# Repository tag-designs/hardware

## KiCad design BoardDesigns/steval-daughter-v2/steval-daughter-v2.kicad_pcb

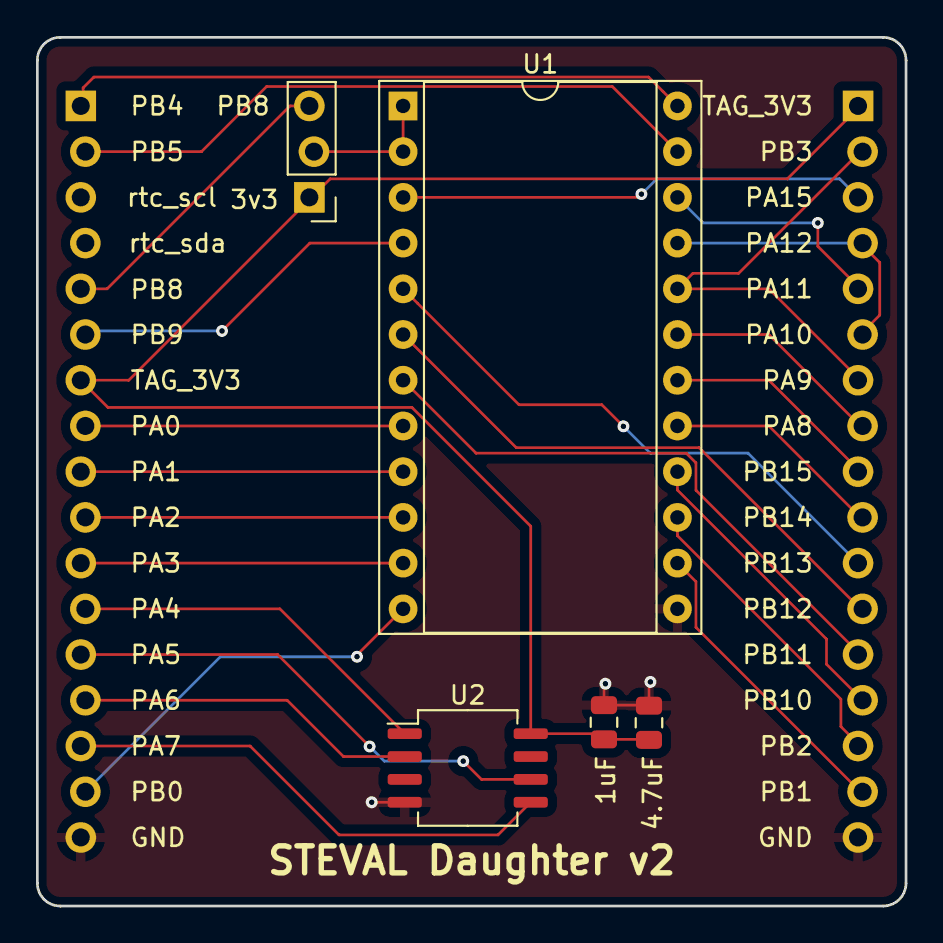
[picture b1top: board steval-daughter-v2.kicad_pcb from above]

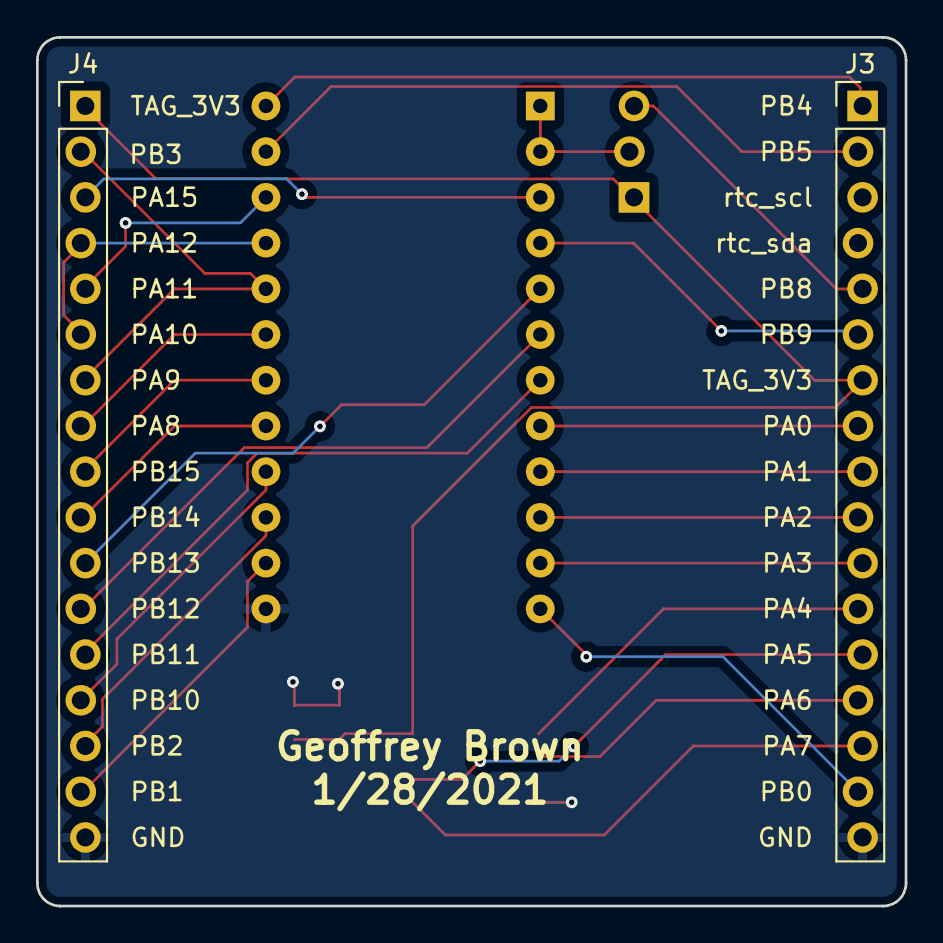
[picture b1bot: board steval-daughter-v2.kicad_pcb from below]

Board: 2 copper layers, 48.3 x 48.3 mm, 7 parts (2 on the bottom side), 29 nets.

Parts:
C1: 4.7uF; C_0805_2012Metric
C2: 1uF; C_0805_2012Metric
J3, J4: Conn_01x17; PinHeader_1x17_P2.54mm_Vertical_Staggered
J101: Conn_01x03; PinHeader_1x03_P2.54mm_Vertical
U1: ST-Steval; DIP-24_W15.24mm_Socket
U2: AT25FF321; SO-8_5.3x6.2mm_P1.27mm

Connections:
/PA0: J3.8, U1.8
/PA1: J3.9, U1.9
/PA2: J3.10, U1.10
/PA3: J3.11, U1.11
/PA4: J3.12, U2.1
/PA5: J3.13, U2.6
/PA6: J3.14, U2.2
/PA7: J3.15, U2.5
/PA8: J4.8, U1.19
/PA9: J4.2, J4.7, U1.20
/PA10: J4.4, J4.6, U1.21
/PA11: J4.5, U1.22
/PA15: J4.3, U1.3
/PB0: J3.16, U1.12
/PB1: J4.16, U1.14
/PB2: J4.15, U1.15
/PB4: J3.1, U1.24
/PB5: J3.2, U1.23
/PB8: J3.5, J101.3
/PB9: J3.6, U1.4
/PB10: J4.14, U1.16
/PB11: J4.13, U1.7
/PB12: J4.12, U1.6
/PB13: J4.11, U1.5
/PB14: J4.10, U1.17
/PB15: J4.9, U1.18
/TAG_3V3: C1.1, C2.1, J3.7, J4.1, J101.1, U2.8
GND: C1.2, C2.2, J3.17, J4.17, U1.13, U2.4
unnamed: J101.2, U1.1, U1.2

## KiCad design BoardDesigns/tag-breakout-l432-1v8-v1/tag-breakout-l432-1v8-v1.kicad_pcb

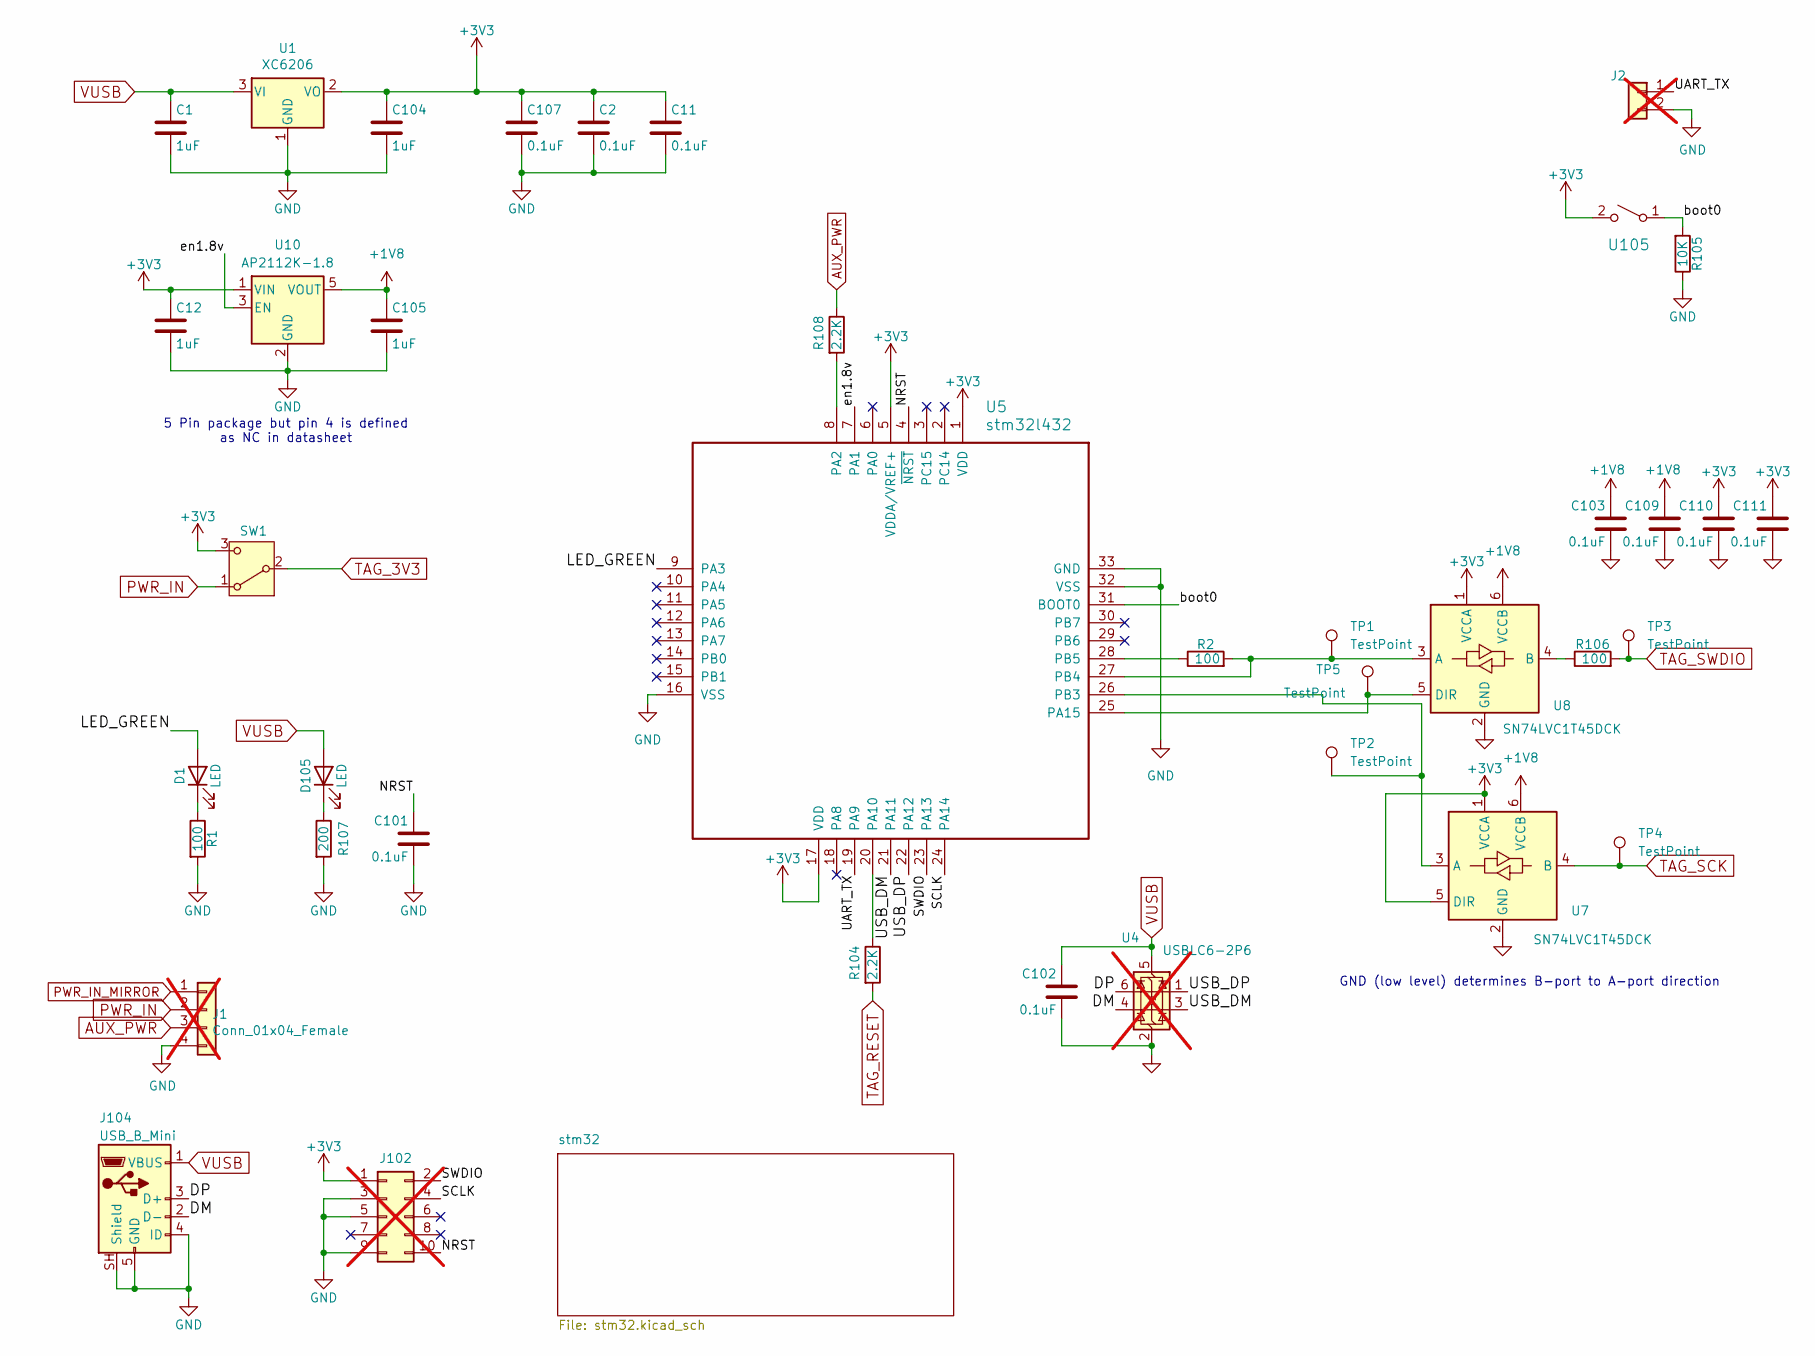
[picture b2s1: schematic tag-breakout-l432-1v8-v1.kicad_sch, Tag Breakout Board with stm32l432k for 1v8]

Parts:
C1, C12, C104, C105: 1uF; C_0402_1005Metric; MPN CL05A105KA5NQNC; LCSC C52923
C2, C11, C101, C102, C103, C107, C109, C110, C111: 0.1uF; C_0402_1005Metric; MPN CL05B104KO5NNNC; LCSC C1525
D1: LED; LED_0805_2012Metric; MPN KT-0805G; LCSC C2297
D105: LED; LED_0603_1608Metric; MPN KT-0603R; LCSC C2286
J1: Conn_01x04_Female; JST_XH_B04B-XH-AM_1x04_P2.50mm_Vertical; not fitted
J2: Conn_01x02_Male; PinHeader_1x02_P2.54mm_Vertical; not fitted
J102: Conn_02x05_Odd_Even; FTSH-105-01-F-D-K; not fitted
J104: USB_B_Mini; USB_Mini-B_Lumberg_2486_01_Horizontal; MPN MINI 5PTP; LCSC C2681563
R1, R2, R106: 100; R_0402_1005Metric; MPN 0402WGF1000TCE; LCSC C25076
R104, R108: 2.2K; R_0402_1005Metric; MPN 0402WGF2201TCE; LCSC C25879
R105: 10K; R_0402_1005Metric; MPN 0402WGF1002TCE; LCSC C25744
R107: 200; R_0402_1005Metric; MPN 0402WGF2000TCE; LCSC C25087
SW1: SW_SPDT; CJS-1200B_NDC; MPN CJS-1200B2; LCSC C35817163
TP1, TP2, TP3, TP4, TP5: TestPoint; TestPoint_Pad_D2.5mm
U1: XC6206; SOT-23-3; MPN XC6206P332MR-G; LCSC C5446
U4: USBLC6-2P6; SOT-666; MPN USBLC6-2P6; LCSC C15999; not fitted
U5: stm32l432; UFQFPN-32-1EP_5x5mm_P0.5mm_EP3.5x3.5mm; MPN STM32L432KBU6TR; LCSC C2928224
U7, U8: SN74LVC1T45DCK; SOT-363_SC-70-6; MPN SN74LVC1T45DCKR; LCSC C9382
U10: AP2112K-1.8; SOT-23-5; MPN AP2112K-1.8TRG1(MS); LCSC C22365428
U105: Tactile Switch; SW_SPST_TS_1187; MPN TS-1187A-C-E-B; LCSC C318889

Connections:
+1V8: C103.1, C105.1, C109.1, U7.6 (VCCB), U8.6 (VCCB), U10.5 (VOUT)
+3V3: C2.1, C11.1, C12.1, C104.1, C107.1, C110.1, C111.1, J102.1, SW1.3 (C), U1.2 (VO), U5.1 (VDD), U5.5 (VDDA/VREF+), U5.17 (VDD), U7.1 (VCCA), U7.5 (DIR), U8.1 (VCCA), U10.1 (VIN), U105.2 (B)
/DM: J104.2 (D-), U4.4 (I/O2)
/DP: J104.3 (D+), U4.6 (I/O1)
/LED_GREEN: D1.2 (A), U5.9 (PA3)
/NRST: C101.1, J102.10, U5.4 (~NRST)
/SCLK: J102.4, U5.24 (PA14)
/SWDIO: J102.2, U5.23 (PA13)
/UART_TX: J2.1, U5.19 (PA9)
/USB_DM: U4.3 (I/O2), U5.21 (PA11)
/USB_DP: U4.1 (I/O1), U5.22 (PA12)
/boot0: R105.2, U5.31 (BOOT0), U105.1 (A)
/en1.8v: U5.7 (PA1), U10.3 (EN)
AUX_PWR: J1.3, R108.1
GND: C1.2, C2.2, C11.2, C12.2, C101.2, C102.2, C103.2, C104.2, C105.2, C107.2, C109.2, C110.2, C111.2, J1.4, J2.2, J102.3, J102.5, J102.9, J104.4 (ID), J104.5 (GND), J104.SH (Shield), R1.2, R105.1, R107.2, U1.1 (GND), U4.2 (GND), U5.16 (VSS), U5.32 (VSS), U5.33 (GND), U7.2 (GND), U8.2 (GND), U10.2 (GND); also elsewhere on the board
unnamed: D1.1 (K), R1.1
unnamed: D105.1 (K), R107.1
unnamed: R108.2, U5.8 (PA2)
unnamed: R104.1, U5.20 (PA10)
unnamed: TP5.1 (1_1), U5.25 (PA15), U8.5 (DIR)
unnamed: TP2.1 (1_1), U5.26 (PB3), U7.3 (A)
unnamed: R2.2, TP1.1 (1_1), U5.27 (PB4), U8.3 (A)
unnamed: R2.1, U5.28 (PB5)
unnamed: R106.1, U8.4 (B)
PWR_IN: J1.2, SW1.1 (A)
PWR_IN_MIRROR: J1.1
TAG_3V3: SW1.2 (B); also elsewhere on the board
TAG_RESET: R104.2; also elsewhere on the board
TAG_SCK: TP4.1 (1_1), U7.4 (B); also elsewhere on the board
TAG_SWDIO: R106.2, TP3.1 (1_1); also elsewhere on the board
VUSB: C1.1, C102.1, D105.2 (A), J104.1 (VBUS), U1.3 (VI), U4.5 (VBUS)

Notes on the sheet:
5 Pin package but pin 4 is defined as NC in datasheet
GND (low level) determines B-port to A-port direction

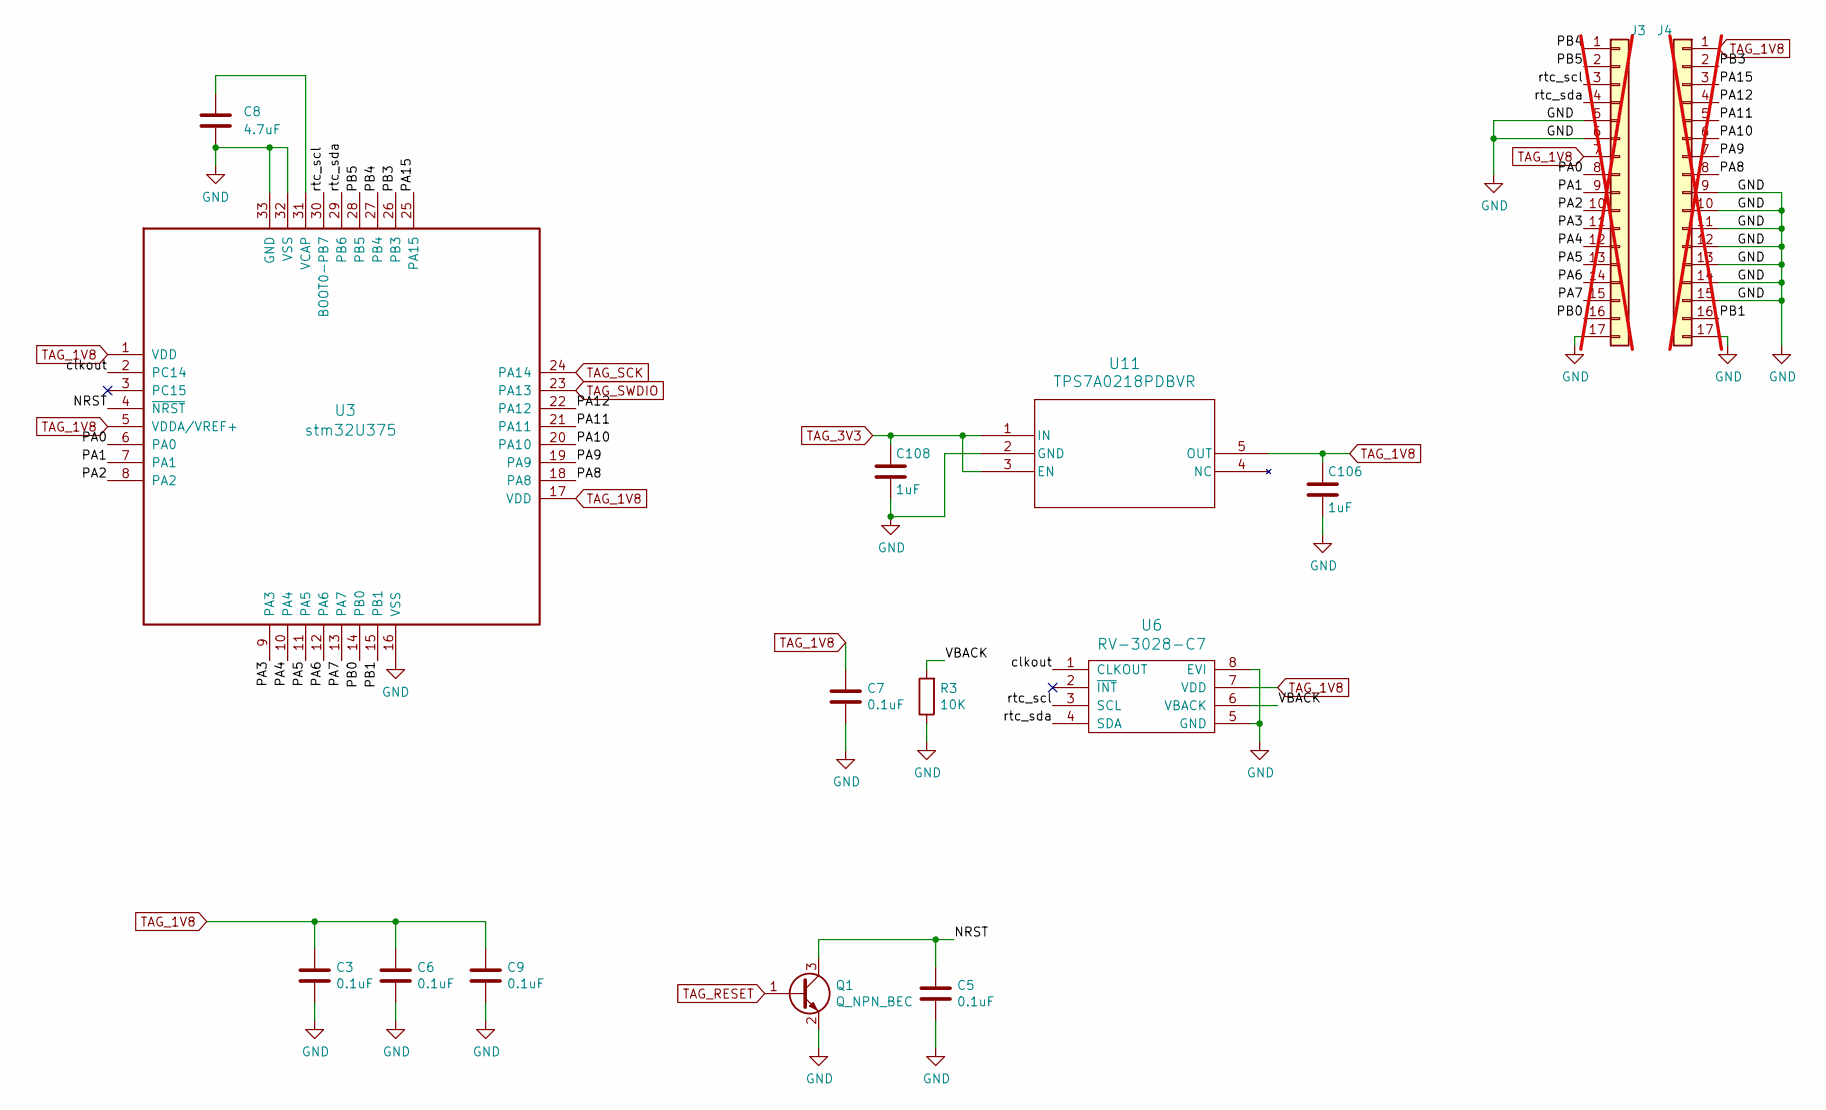
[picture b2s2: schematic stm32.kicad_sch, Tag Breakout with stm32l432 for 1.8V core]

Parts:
C3, C5, C6, C7, C9: 0.1uF; C_0402_1005Metric; MPN CL05B104KO5NNNC; LCSC C1525
C8: 4.7uF; C_0402_1005Metric; MPN CL05A475MP5NRNC; LCSC C23733
C106, C108: 1uF; C_0402_1005Metric; MPN CL05A105KA5NQNC; LCSC C52923
J3, J4: Conn_01x17; PinHeader_1x17_P2.54mm_Vertical_Staggered; not fitted
Q1: Q_NPN_BEC; SOT-23; MPN BCX70H,215; LCSC C20527
R3: 10K; R_0402_1005Metric; MPN 0402WGF1002TCE; LCSC C25744
U3: stm32U375; UFQFPN-32-1EP_5x5mm_P0.5mm_EP3.5x3.5mm; MPN STM32U375KGU6; LCSC C45338536
U6: RV-3028-C7; RV-8803-C7; MPN RV-3028-C7-32.768kHz-1ppm-TA-QC; LCSC C3019759
U11: TPS7A0218PDBVR; SOT-23-5; MPN TPS7A0218PDBVR; LCSC C3748843

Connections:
/stm32/NRST: C5.1, Q1.3 (C), U3.4 (~NRST); also elsewhere on the board
/stm32/PA0: J3.8, U3.6 (PA0)
/stm32/PA1: J3.9, U3.7 (PA1)
/stm32/PA2: J3.10, U3.8 (PA2)
/stm32/PA3: J3.11, U3.9 (PA3)
/stm32/PA4: J3.12, U3.10 (PA4)
/stm32/PA5: J3.13, U3.11 (PA5)
/stm32/PA6: J3.14, U3.12 (PA6)
/stm32/PA7: J3.15, U3.13 (PA7)
/stm32/PA8: J4.8, U3.18 (PA8)
/stm32/PA9: J4.7, U3.19 (PA9)
/stm32/PA10: J4.6, U3.20 (PA10)
/stm32/PA11: J4.5, U3.21 (PA11)
/stm32/PA12: J4.4, U3.22 (PA12)
/stm32/PA15: J4.3, U3.25 (PA15)
/stm32/PB0: J3.16, U3.14 (PB0)
/stm32/PB1: J4.16, U3.15 (PB1)
/stm32/PB3: J4.2, U3.26 (PB3)
/stm32/PB4: J3.1, U3.27 (PB4)
/stm32/PB5: J3.2, U3.28 (PB5)
/stm32/VBACK: R3.2, U6.6 (VBACK)
/stm32/clkout: U3.2 (PC14), U6.1 (CLKOUT)
/stm32/rtc_scl: J3.3, U3.30 (PB7), U6.3 (SCL)
/stm32/rtc_sda: J3.4, U3.29 (PB6), U6.4 (SDA)
GND: C3.2, C5.2, C6.2, C7.2, C8.1, C8.2, C9.2, C106.2, C108.2, J3.5, J3.6, J3.17, J4.9, J4.10, J4.11, J4.12, J4.13, J4.14, J4.15, J4.17, Q1.2 (E), R3.1, U3.16 (VSS), U3.31 (BOOT0), U3.32 (VSS), U3.33 (GND), U6.5 (GND), U6.8 (EVI), U11.2 (GND); also elsewhere on the board
TAG_1V8: C3.1, C6.1, C7.1, C9.1, C106.1, J3.7, J4.1, U3.1 (VDD), U3.5 (VDDA/VREF+), U3.17 (VDD), U6.7 (VDD), U11.5 (OUT)
TAG_3V3: C108.1, U11.1 (IN), U11.3 (EN); also elsewhere on the board
TAG_RESET: Q1.1 (B); also elsewhere on the board
TAG_SCK: U3.24 (PA14); also elsewhere on the board
TAG_SWDIO: U3.23 (PA13); also elsewhere on the board

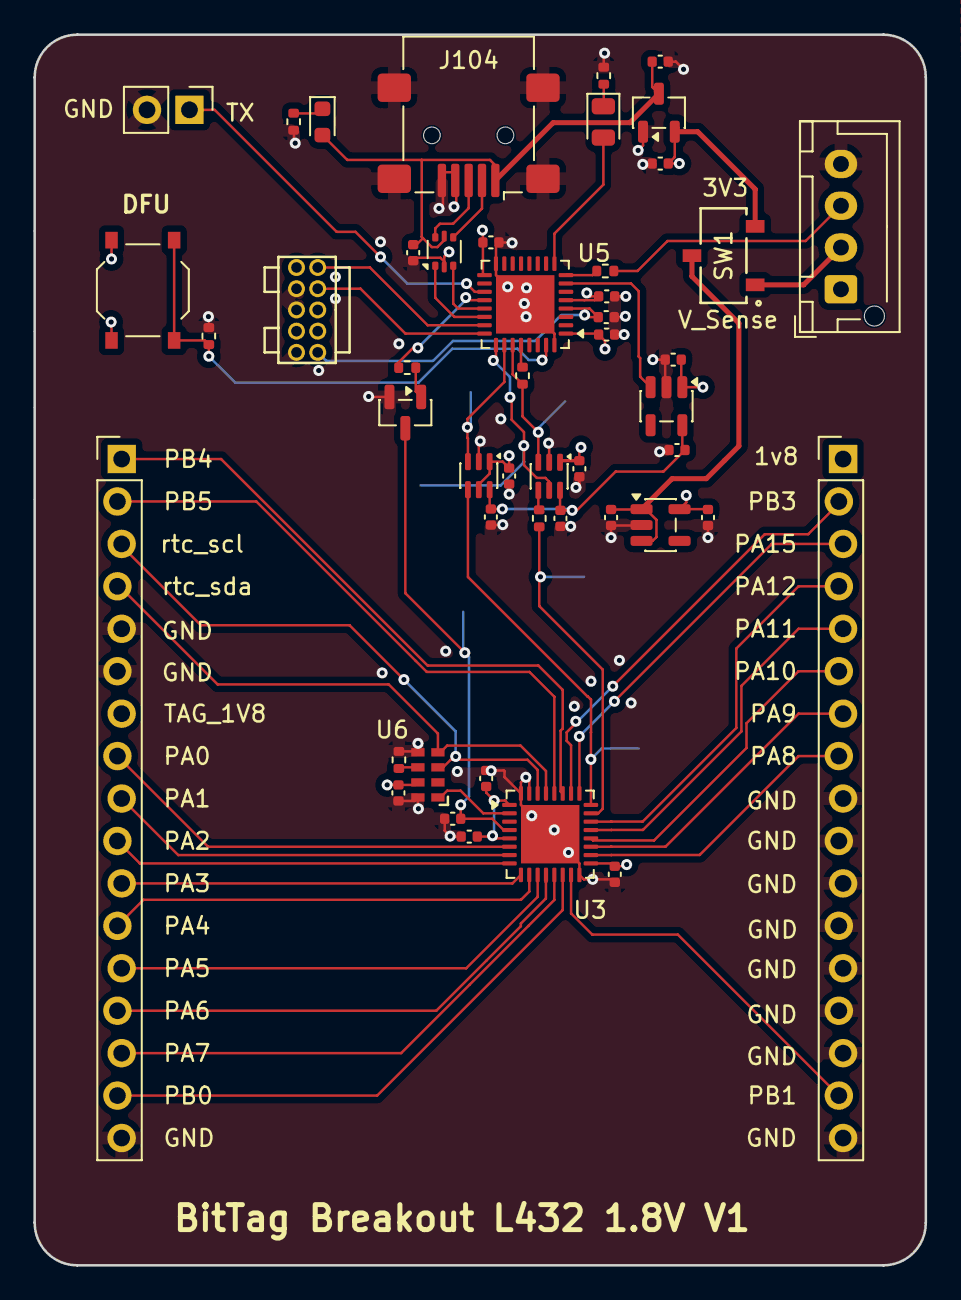
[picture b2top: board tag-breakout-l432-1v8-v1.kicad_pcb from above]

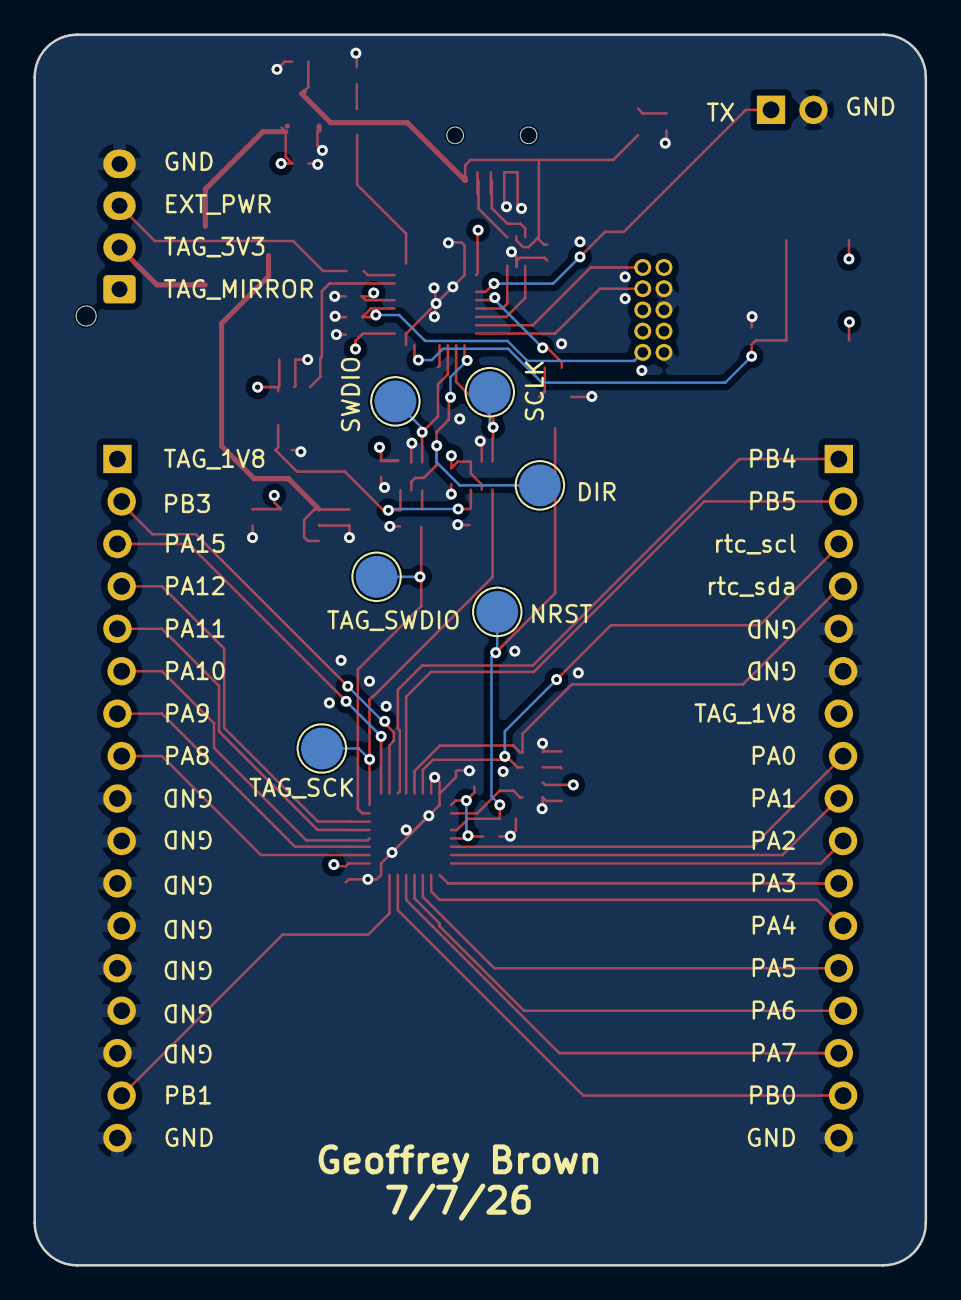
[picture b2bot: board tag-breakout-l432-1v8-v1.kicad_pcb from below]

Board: 4 copper layers, 53.3 x 73.7 mm, 54 parts (6 on the bottom side), 55 nets.

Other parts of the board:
TP7: TestPoint; TestPoint_Pad_D2.5mm

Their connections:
/stm32/NRST: TP7.1 (1_1); also elsewhere on the board

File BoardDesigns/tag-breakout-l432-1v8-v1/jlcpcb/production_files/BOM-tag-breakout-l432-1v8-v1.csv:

Comment,Designator,Footprint,LCSC,Quantity
0.1uF,"C101,C102,C103,C107,C109,C11,C110,C111,C2,C3,C5,C6,C7,C9",C_0402_1005Metric,C1525,14
100,"R1,R106,R2",R_0402_1005Metric,C25076,3
10K,"R105,R3",R_0402_1005Metric,C25744,2
1uF,"C1,C104,C105,C106,C108,C12",C_0402_1005Metric,C52923,6
2.2K,"R104,R108",R_0402_1005Metric,C25879,2
200,R107,R_0402_1005Metric,C25087,1
AP2112K-1.8,U10,SOT-23-5,C22365428,1
LED,D105,LED_0603_1608Metric,C2286,1
LED,D1,LED_0805_2012Metric,C2297,1
Q_NPN_BEC,Q1,SOT-23,C20527,1
RV-3028-C7,U6,RV-8803-C7,C3019759,1
SN74LVC1T45DCK,"U7,U8",SOT-363_SC-70-6,C9382,2
SW_SPDT,SW1,CJS-1200B_NDC,C35817163,1
TPS7A0218PDBVR,U11,SOT-23-5,C3748843,1
Tactile Switch,U105,SW_SPST_TS_1187,C318889,1
USBLC6-2P6,U4,SOT-666,C15999,1
USB_B_Mini,J104,USB_Mini-B_Lumberg_2486_01_Horizontal,C2681563,1
XC6206,U1,SOT-23-3,C5446,1
stm32l432,"U3,U5",UFQFPN-32-1EP_5x5mm_P0.5mm_EP3.5x3.5mm,C2928224,2
